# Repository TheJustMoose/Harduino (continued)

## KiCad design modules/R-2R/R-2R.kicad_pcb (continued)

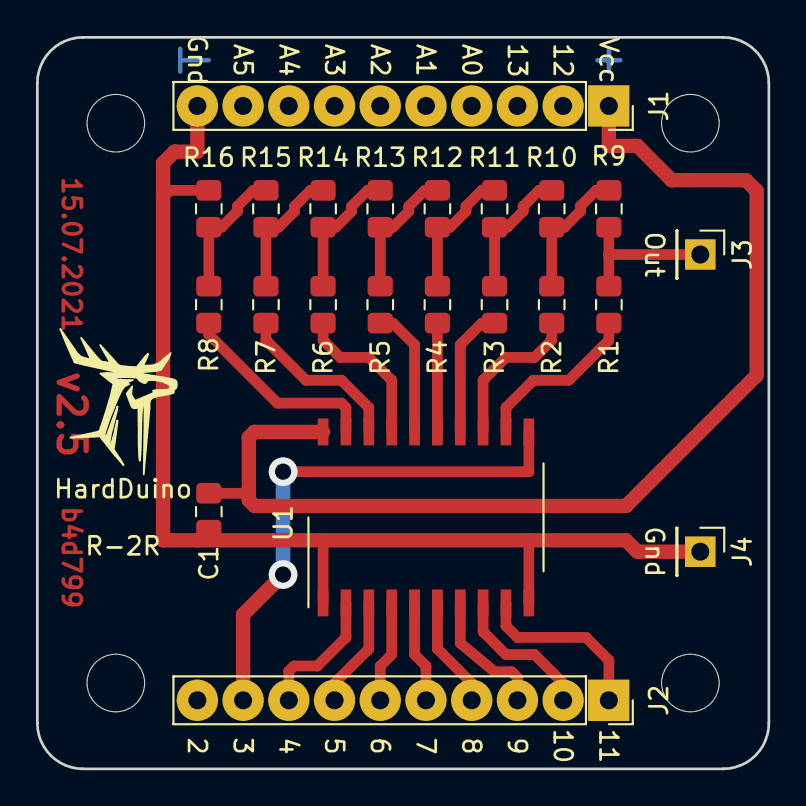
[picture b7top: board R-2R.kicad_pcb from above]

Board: 2 copper layers, 40.6 x 40.6 mm, 26 parts (0 on the bottom side), 27 nets.

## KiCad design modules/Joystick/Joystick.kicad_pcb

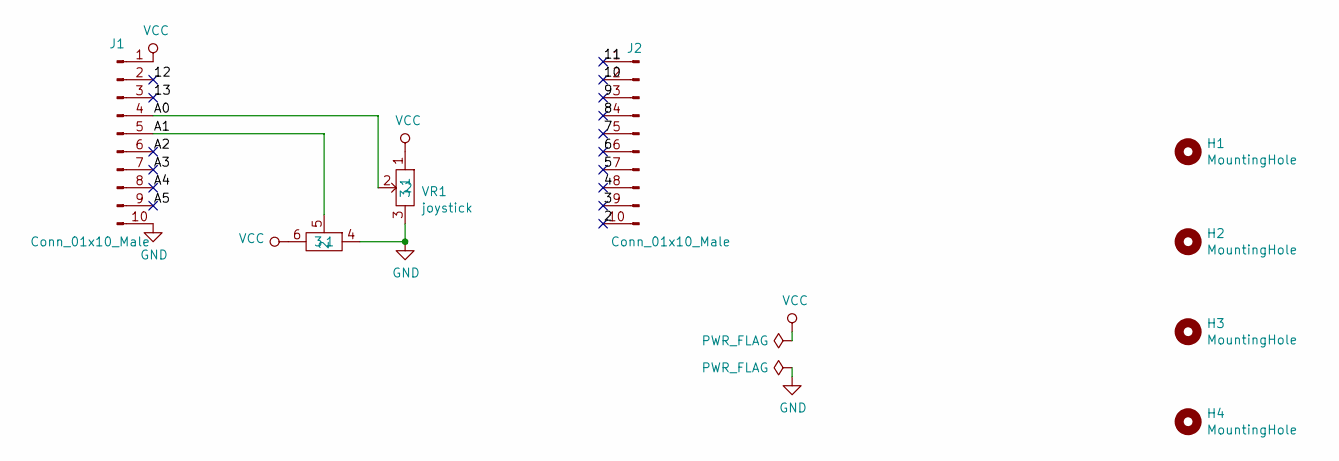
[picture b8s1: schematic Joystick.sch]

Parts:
H1, H2, H3, H4: MountingHole; MountingHole_3.2mm_M3
J1, J2: Conn_01x10_Male; PinSocket_1x10_P2.54mm_Vertical
VR1: joystick; Joystick

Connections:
/2: J2.10
/3: J2.9
/4: J2.8
/5: J2.7
/6: J2.6
/7: J2.5
/8: J2.4
/9: J2.3
/10: J2.2
/11: J2.1
/12: J1.2
/13: J1.3
/A0: J1.4, VR1.2
/A1: J1.5, VR1.5 (2)
/A2: J1.6
/A3: J1.7
/A4: J1.8
/A5: J1.9
GND: J1.10, VR1.3, VR1.4 (1)
VCC: J1.1, VR1.1, VR1.6 (3)

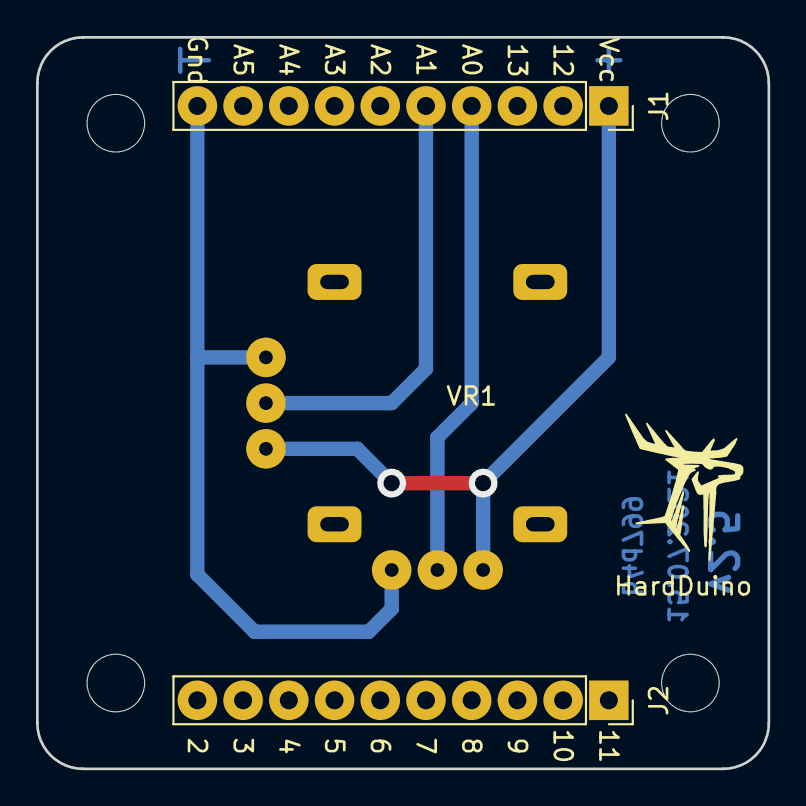
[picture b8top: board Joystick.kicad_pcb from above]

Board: 2 copper layers, 40.6 x 40.6 mm, 7 parts (0 on the bottom side), 4 nets.

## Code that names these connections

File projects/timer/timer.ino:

#include <TimerOne.h>
#include <EEPROM.h>

// hardware:
// 3 tactile button + rotary encoder button
// 74HC139 decoder

// connections:
// pin 12 == PB4 -> A0 pcb -> 13 (A1|B) decoder pin
// pin 13 == PB5 -> A1 pcb -> 14 (A0|A) decoder pin
// pin A2 == PC2 -> all tactile buttons + pullup
// pin A1 == PC1 -> rotary encoder pin A
// pin A0 == PC0 -> rotary encoder pin B
// pin 8-11 == PB0-3 -> 74LS247 pins A-D
// pin 2 -> decimal point

// Do not use "const byte" here, it's not work
// Input ports
#define ENC_PORT PINC
#define BTN_PORT PINC
#define BTN_BIT  2

// Output ports
#define DIG_PORT PORTB
#define DIG_BIT_B 4  // 74HC139
#define DIG_BIT_A 5

#define NUM_PORT PORTB
#define NUM_BIT_0 0  // 74LS247
#define NUM_BIT_1 1
#define NUM_BIT_2 2
#define NUM_BIT_3 3

const int dp = 2;  // decimal point
const int buzzer = 3;
const int line = 4;  // buttons state
const int mosfet1 = 5;

const int d0 = 8;
const int d1 = 9;
const int d2 = 10;
const int d3 = 11;

const int a0 = 13;  // yes! it's fail :(
const int a1 = 12;

const int del = 5; // delay ms

uint8_t btn_was_pressed[4] = {0, 0, 0, 0};
uint8_t btn_pressed[4] = {0, 0, 0, 0};
uint8_t LED[4] = {0, 0, 0, 0}; // the numbers on the LED
uint8_t digit = 0; // current processed digit | button
boolean in_edit = true;
uint16_t counter = 0;  // how many times timer interrupt was called
int16_t rest_of_time = 0;
bool should_update = false;

void set_addr(uint8_t addr) {
  // PB5 == A decoder pin
  if (addr & 0x01)
    bitSet(DIG_PORT, DIG_BIT_A);
  else
    bitClear(DIG_PORT, DIG_BIT_A);

  // PB4 == B decoder pin
  if (addr & 0x02)
    bitSet(DIG_PORT, DIG_BIT_B);
  else
    bitClear(DIG_PORT, DIG_BIT_B);
}

void set_number(uint8_t number) {
  if (number & 0x01)
    bitSet(NUM_PORT, NUM_BIT_0);
  else
    bitClear(NUM_PORT, NUM_BIT_0);

  if (number & 0x02)
    bitSet(NUM_PORT, NUM_BIT_1);
  else
    bitClear(NUM_PORT, NUM_BIT_1);

  if (number & 0x04)
    bitSet(NUM_PORT, NUM_BIT_2);
  else
    bitClear(NUM_PORT, NUM_BIT_2);

  if (number & 0x08)
    bitSet(NUM_PORT, NUM_BIT_3);
  else
    bitClear(NUM_PORT, NUM_BIT_3);
}

void on() {
  digitalWrite(mosfet1, HIGH);
  Serial.println("ON");
}

void off() {
  digitalWrite(mosfet1, LOW);
  Serial.println("OFF");
}

void beep() {
  for (int i = 0; i < 3; i++) {
    digitalWrite(buzzer, HIGH);
    delay(150);
    digitalWrite(buzzer, LOW);
    delay(200);
  }
}

void check_buttons() {
  byte val = BTN_PORT;
  boolean vbl = val & _BV(BTN_BIT);
  if (!vbl) {
    if (btn_was_pressed[digit])
      btn_pressed[digit] = true;
    else
      btn_was_pressed[digit] = true;
  } else {
    btn_pressed[digit] = false;
    btn_was_pressed[digit] = false;
  }
}

/* returns change in encoder state (-1,0,1) */
int8_t read_encoder() {
  static int8_t enc_states[] = {0,1,-1,0,0,0,0,0,0,0,0,0,0,0,0,0};
  static uint8_t old_AB = 0;

  old_AB <<= 2;                   // remember previous state
  old_AB |= ( ENC_PORT & 0x03 );  // add current state
  return (enc_states[( old_AB & 0x0f )]);
}

void on_tmr() {
  digit++;
  if (digit >= 4)
    digit = 0;

  set_addr(digit);
  set_number(LED[digit]);
  check_buttons();

  if (in_edit)
    return;

  counter++;
  if (counter < 1000)
    return;

  counter = 0;
  rest_of_time--;
  should_update = true;
}

void setup() {
  // put your setup code here, to run once:
  Timer1.initialize(1000); // in us
  Timer1.attachInterrupt(on_tmr);

  pinMode(line, INPUT);

  pinMode(dp, OUTPUT);
  pinMode(buzzer, OUTPUT);
  pinMode(mosfet1, OUTPUT);

  pinMode(d0, OUTPUT);
  pinMode(d1, OUTPUT);
  pinMode(d2, OUTPUT);
  pinMode(d3, OUTPUT);

  pinMode(a0, OUTPUT);
  pinMode(a1, OUTPUT);

  
  digitalWrite(dp, LOW);
  digitalWrite(buzzer, LOW);
  digitalWrite(mosfet1, LOW);

  digitalWrite(d0, LOW);
  digitalWrite(d1, LOW);
  digitalWrite(d2, LOW);
  digitalWrite(d3, LOW);

  digitalWrite(a0, LOW);
  digitalWrite(a1, LOW);

  Serial.begin(115200);
  Serial.println("Start");

  rest_of_time = load();
  update_led();
}

void save(uint16_t val) {
  uint8_t low = val & 0xFF;
  EEPROM.write(0, low);

  uint8_t high = val >> 8;
  EEPROM.write(1, high);
}

uint16_t load() {
  uint8_t low = EEPROM.read(0);
  uint8_t high = EEPROM.read(1);
  return (high << 8) + low;
}

void update_led() {
  int t = rest_of_time;
  LED[0] = t % 10;
  t /= 10;
  LED[1] = t % 10;
  t /= 10;
  LED[2] = t % 10;
  t /= 10;
  LED[3] = t % 10;
  t /= 10;
}

void edit() {
  int8_t zoom = btn_pressed[3] ? 10 : 1;
  int8_t tmp = read_encoder()*zoom;
  if (tmp) {
    Serial.print(tmp);
    Serial.print(" ");
    rest_of_time += tmp;
    if (rest_of_time < 0)
      rest_of_time = 0;
    if (rest_of_time > 9999)
      rest_of_time = 9999;
    Serial.println(rest_of_time);
    update_led();
  }
  
  if (btn_pressed[2]) {
    if (rest_of_time) {
      save(rest_of_time);
      counter = 0;
      in_edit = false;
      on();
    }
    Serial.println("Start");
    return;
  }
  
  if (btn_pressed[1]) {
    Serial.println("btn 1 pressed");
  }
  
  if (btn_pressed[2]) {
    Serial.println("btn 2 pressed");
  }
}

void timer() {
  if (btn_pressed[1]) {
    off();
    in_edit = true;
    rest_of_time = load();
    update_led();
    return;
  }

  if (!should_update)
    return;

  if (!rest_of_time) {
    off();
    in_edit = true;
    update_led();
    beep();
    rest_of_time = load();
  }
  
  update_led();
  should_update = false;
}

void loop() {
  if (in_edit)
    edit();
  else
    timer();
}

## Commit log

2019-09-12 Add description Fix template
2019-09-12 Add ICs, LEDs and MOSFETs
2019-09-13 Add 6x6 tactile button
2019-09-13 Add buttons. Place components on PCB.
2019-09-13 In work
2019-09-14 Ready!
2019-09-15 Btns & rotary encoder
2019-09-15 Add crlf
2019-09-15 Just modules table
2019-09-16 Add more colors
2019-09-18 Add device table
2019-09-19 8x8 LED matrix
2019-09-19 Add some shields, move some pins
2019-09-19 Add alternate kbd
2019-09-20 Add some colors
2019-09-20 Add piezo
2019-09-20 Add LEDs
2019-09-20 A0 == pin 12 A1 == pin 13
2019-09-23 Add connectors module
2019-09-23 Add title
2019-09-23 Add RTC pcb
2019-09-23 RTC pcb + CR1220 holder
2019-09-24 Fix silk
2019-09-24 Replace 1N4148W -> LL4148
2019-09-24 Valcoder in work
2019-09-24 Enable pin not required
2019-09-25 Valcoder pcb ready
2019-09-25 Add raw keyboard
2019-09-25 Add connector modules
2019-09-26 Place connectors
2019-09-26 Try to add some traces to 2x board
2019-09-26 just cache
2019-09-26 Harduino module
2019-09-26 h2x ready
2019-09-27 Connect AVR to pins
2019-09-27 Fix via size
2019-09-28 Place AVR in PCB
2019-09-28 Harduino in DIP
2019-10-01 'Resque ATmega'
2019-10-02 Add silk
2019-10-02 LED small fixes (move cap & silk)
2019-10-03 HarduinoDIP in work
2019-10-04 Harduino in work
2019-10-04 Trace it! Harduino ready.
2019-10-04 Fix RX/TX pins order
2019-10-06 Lost Vcc!!!
2019-10-07 Move R/C to another side
2019-10-07 Pull-up 74HS139
2019-10-08 Oops. 4511 is active high
2019-10-08 Harduino small fixes
2019-10-08 LED in work. Again.
2019-10-10 Just kbd 3x4
2019-10-11 LED rework
2019-10-12 Fix LED pcb
2019-10-12 v0.0
2019-10-12 PCB template
2019-10-13 Lost values
2019-10-15 An attempt to decide which modules are needed for which devices
2019-10-15 One more device
2019-11-04 Center pcb. Add photomask in pdf.
2020-02-18 Freq meter
2020-02-19 Raw Kbd in work
2020-02-19 Raw Kbd is ready
2020-02-19 Sensor Shield
2020-02-20 Harduino -> HardDuino
2020-02-20 Fix template
2020-02-20 L293 shield template
2020-02-20 L293
2020-02-20 Small fixes
2020-02-20 L293 sch
2020-02-21 L293 pcb
2020-02-21 Some bak files
2020-02-21 L293 pcb ready
2020-02-22 Add photomask in pdf.
2020-02-24 Fix pullup
2020-02-28 Reorder some pins
2020-02-28 Move some rows
2020-02-28 Kbd may be two different sizes
2020-03-01 Test code for shield
2020-03-01 Test code for LED shield
2020-03-02 Add pull-up and cap
2020-03-02 Arrow kbd
2020-03-02 Fix BigTrak modules
2020-03-02 Calculator
2020-03-02 Reorder & fix
2020-03-02 Barrier
2020-03-03 Place Arrow Keys
2020-03-03 Arrow Kbd ready
2020-03-04 Add date. Add polygon.
2020-03-04 Add gnd symbol
2020-03-05 Portrait page
2020-03-05 Pins (Sensor shield)
2020-03-05 Add some pinheaders
2020-03-06 Pins (sensor) shield ready
2020-03-06 Add pictures
2020-03-06 Add icon
2020-03-07 Add logo-moose!
2020-03-08 Remove comment
2020-03-08 Some changes
2020-03-09 Test code for arrow kbd
2020-03-09 Lost labels
2020-03-09 Add photomask in pdf. Add gerber.
2020-03-10 Horizontal Sensor Shield
2020-03-10 Add logo to template
2020-03-10 Done!
2020-03-11 h2x + Sensor Shield
2020-03-11 I want some modules...
2020-03-11 h2x with Sensor Shield in work
2020-03-11 Buzzer test
2020-03-12 Sensor Shield ready
2020-03-12 Add modules count
2020-03-13 MOSFET shield is ready
2020-03-13 Replace SOT23-5 to TSSOP5
2020-03-13 Add L4940 to motor shield
2020-03-13 Add stab to motor shield
2020-03-13 Update description & image
2020-03-15 Done
2020-03-16 Enlarge pads. Add photomask.
2020-03-16 Add counts
2020-03-16 Fix photomask
2020-03-17 Another side
2020-03-25 Replace 10 x 1pin sockets -> 1 x 10pin socket
2020-03-25 h2xS version 2
2020-03-25 Fix holes and edges
2020-03-25 Place pinheaders
2020-03-25 Silk
2020-03-25 Copy&paste some tracks from old pcb
2020-03-25 h2xS v2 in work
2020-03-26 h2xS v2 ready
2020-03-26 Small fixes L293
2020-03-28 h2xSv2. Add photomask in pdf.
2020-03-28 L293. Add photomask in pdf.
2020-04-04 Test code for rotary encoder
2020-04-05 Add comment
2020-04-05 Pins number changed. Awful.
2020-04-06 Motor shield v2 in work Attention! Pin numbers changed!
2020-04-07 L293 in work.
2020-04-08 Motor shield is ready
2020-04-08 LED v2 Pins changed
2020-04-08 Fix date size
2020-04-08 Fix LED description
2020-04-08 Add resistor
2020-04-09 Decrease some tracks
2020-04-11 Move resistor. Add net label.
2020-04-13 RC project
2020-04-13 Add jumper for decimal point. Small fixes.
2020-04-14 LED. Add photomask in pdf.
2020-04-16 74LS139 from KiCAD library is not Ok It has wrong pin A & B in both decoders I fix test code cause I can't fix pcb :(
2020-04-17 Fix pin numbering to v2
2020-04-17 MOSFET v2 pcb is ready. Change pin numbering. Add photomask.
2020-04-17 Fix some tracks
2020-04-17 Move pdf into subfolder
2020-04-18 Raw Kbd. Fix some tracks. Add photomask in pdf.
2020-04-18 Joystick shield
2020-04-19 Move to tests dir
2020-04-19 Just rename folder
2020-04-19 Add version, date and git hash Fix pinheader pad sizes
2020-04-19 LCD shield in work
2020-04-21 LCD btns
2020-04-22 Joystick. Page settings
2020-04-22 R-2R shield is ready
2020-04-22 R-2R, polishing
2020-04-22 R-2R. Add photomask in pdf.
2020-04-22 LCD is ready
2020-04-22 LCD. Add photomask in pdf.
2020-04-22 Fix links ;)
2020-04-23 Add link to joystick
2020-04-23 Plans
2020-04-24 utf-8
2020-04-25 ArrowKbd v2. Change pin assigning
2020-04-25 ArrowKbd. Add photomask in pdf.
2020-04-25 ArrowKbd. Update photomask in pdf.
2020-04-25 Kbd. Lost tracks.
2020-04-25 Kbd, test code
2020-04-25 R-2R test
2020-04-26 LED pcb is ready
2020-04-26 LEDs. Add photomask in pdf.
2020-04-26 Fix LCD pins
2020-04-26 Kbd v2. Fixed pin numbering.
2020-04-26 Kbd. Add photomask in pdf.
2020-04-27 18xLED
2020-04-27 Lost pot
2020-04-30 My LCD does not have LED resistor :( Add silk etc
2020-05-02 LCD test code
2020-05-02 Kbd test code
2020-05-04 One more shield
2020-05-05 h3xS in work
2020-05-07 HardDuino polishing
2020-05-07 ArrowKbd polishing
2020-05-10 Remove Harduino module cause it's awful
2020-05-10 Add HardDuino TQFP module
2020-05-10 HardDuino TQFP is ready
2020-05-16 HardDuino TQFP polishing
2020-05-16 HardDuino
2020-05-16 LED polishing
2020-05-16 Update hash
2020-05-23 LCD. Enlarge pads, straighten some tracks
2020-05-23 Fix hash. Add photomask in pdf.
2020-05-23 HardDuinoTQFP polishing
2020-05-23 HardDuinoTQFP. Move pcb, add photomask
2020-05-30 HardDuinoTQFP: fix pin numbering (8 and 12 was mixed up) Add ISP pinheader
2020-05-31 HardDuinoTQFP. Add photomask & hash
2020-06-01 HardDuinoTQFP: add protection, remove AREF
2020-06-17 Clock project. Initial commit.
2020-06-17 Clock project. Bug fixing.
2020-11-01 Timer. Initial commit.
2020-11-01 Some test code
2020-11-01 Moose. Just Moose!
2020-11-03 Timer works!
2020-11-06 Fix sizes
2020-11-06 Fix 74LS139 pins
2020-11-06 Add hash, fix labels
2020-11-07 Try to create 16 smd buttons kbd
2020-11-07 remove fp-info-cache
2020-11-07 Fix description
2020-11-07 Add .gitignore with cache
2020-11-07 Some fixes
2020-11-07 Some fixes (project options)
2020-11-07 Fix hash, add gerber
2020-11-07 Fix pins, add versions description
2020-11-07 Remove a few of solder mask
2020-11-07 Lost gerber
2020-11-07 Replace 2N7000 -> IRLML
2020-11-07 Add hash
2020-11-11 New h3xSv2 is ready
2020-11-11 Add hash & gerber
2020-11-11 Add labels
2020-11-11 Valcoder polishing
2020-11-11 Fix hash, fix gerber
2020-11-12 L293 motor driver v2
2020-11-12 Motor shield polishing
2020-11-13 Add legend to LED
2020-11-17 Timer bug-fixing
2020-11-22 HardDuino small fixes
2020-11-22 This is hybrid. It contains HardDuino TQFP and h2xS.
2020-11-23 HardDuinoTQFP. Fix hash, add gerber...
2020-11-24 Add links to instagram
2020-11-24 Mistype
2020-11-24 Add diodes to LCD btns PCB. Add gerber.
2020-11-24 LCD polishing
2020-11-24 Ideas, fixing, etc
2020-11-26 Polishing. Fix table header, fix some mistypes
2020-11-27 A4988 shield
2020-11-27 A4988. Fix hash, add gerber.
2020-11-28 A4988. Fix pin names
2020-11-28 L293. Reverse polarity protection is added.
2020-11-28 Add 74LS139 for kbd
2020-11-28 Add description
2020-11-29 Move *.pdf into pdf/
2020-11-29 Fix shields description
2020-11-29 Files is not required
2020-12-03 LED. IC names is added.
2020-12-03 LED. Fix hash, add gerber.
2020-12-05 SmdKbd in work
2020-12-05 Valc. Add silk.
2021-01-08 TPIC6C595 was added to library
2021-02-18 Wrong PCB orientation! Swap pinheader :( Smaller holes for LCD. Add pull-ups, add pin names.
2021-02-18 LCD. Fix hash.
2021-02-18 LCD btns. Add pin names.
2021-02-18 KiCAD update some files
2021-02-19 LCD. Fix grid to 2.54, fix mounting holes position. This version is uncompatible with previous!!
2021-02-19 h2xSv2 - Fix grid to 2.54 & mounting holes
2021-02-20 1x PCBs. Move holes to edges. Caution! This changes is uncompatible with previous versions...
2021-02-21 Now 2x shields have distance between 1x parts
2021-02-21 LCD. Pot was moved.
2021-02-21 A4988. Add jumpers & pull-ups, FIX SOCKET!, polishing
2021-02-21 Fix hash & version
2021-02-21 A4988, add photomask
2021-02-23 Rename pins. I don't know where I got old names but I found new names on A4988 pcb.
2021-02-23 HardDuino. Fix port name.
2021-02-23 Fix hashes
2021-02-23 Test code for A4988 shield
2021-04-04 Fix left Edge.Cuts
2021-06-13 Move mounting holes closer
2021-06-17 v2.5, size was changed to 31.1 x 31.92
2021-06-20 Fix LCD sizes and LCD shield
2021-06-21 h2xSv2 - now v2.5
2021-06-30 Replace pot
2021-06-30 LCD, add photomask
2021-07-10 LCD shield. Data lines was moved to another socket.
2021-07-11 Fix routes on h2xS
2021-07-11 New hash on h2xS
2021-07-13 h2xS fix date & hash. Add photomask.
2021-07-13 LCD fix date & hash. Add photomask.
2021-07-13 h2xS - Reverse polarity protection was added
2021-07-13 h2xS fix hash. Add photomask.
2021-07-13 All 1x shields was rotated clockwise
2021-07-14 Util to check Mounting Holes on PCBs
2021-07-14 Now all mounting holes have distance 31.92 x 31.1
